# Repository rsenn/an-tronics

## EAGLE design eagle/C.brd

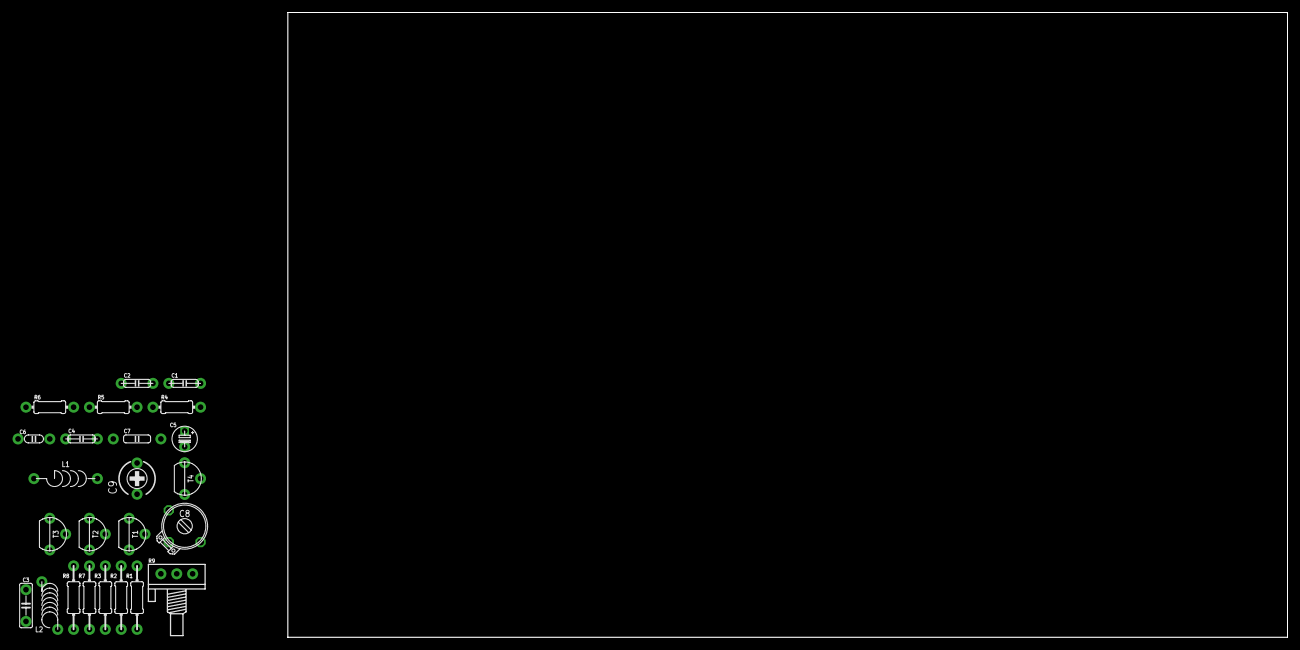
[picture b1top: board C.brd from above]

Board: 2 copper layers, 160.0 x 100.0 mm, 24 parts (0 on the bottom side), 14 nets, no tracks yet.

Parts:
C1, C2: C050-020X044
C3: 10nF; C050-025X060
C4: 10nF; C050-020X044
C5: 100μF; E2.5-4/V
C6: 22pF; C050-020X036
C7: 100nF; C075-020X044
C8: 20pF; TRIM-2222-808
C9: 5pF; CTRIMTZ03
L1: 2.2μH; L-03/10
L2: L-04/8V
R1, R2: 4.7kΩ; 0204/10-V
R3: 0204/10-V
R4, R5: 1MΩ; 0204/7
R6: 56kΩ; 0204/7
R7: 10kΩ; 0204/10-V
R8: 470kΩ; 0204/10-V
R9: 10kΩ; POT
T1, T2, T3, T4: TO92-CBE-A

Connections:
unnamed: C1.2, R5.1, T2.2
unnamed: C2.1, R2.2, R5.2, T2.1
unnamed: C1.1, R1.2, R4.2, T1.1
unnamed: C2.2, R6.1, T3.2
unnamed: C3.1, R3.2, R6.2, T3.1
unnamed: C4.2, R4.1, T1.2
unnamed: C4.1, L1.1
unnamed: C5.+, R1.1, R2.1, R3.1, R7.1, R9.A
unnamed: C7.2, R8.2, T4.2
unnamed: R8.1, R9.S
unnamed: C8.2, C9.2, L2.2, T4.1
unnamed: C6.2, C7.1, L1.2, L2.1, R7.2
unnamed: C6.1, C8.1, C9.1
unnamed: C3.2, C5.-, R9.E, T1.3, T2.3, T3.3, T4.3

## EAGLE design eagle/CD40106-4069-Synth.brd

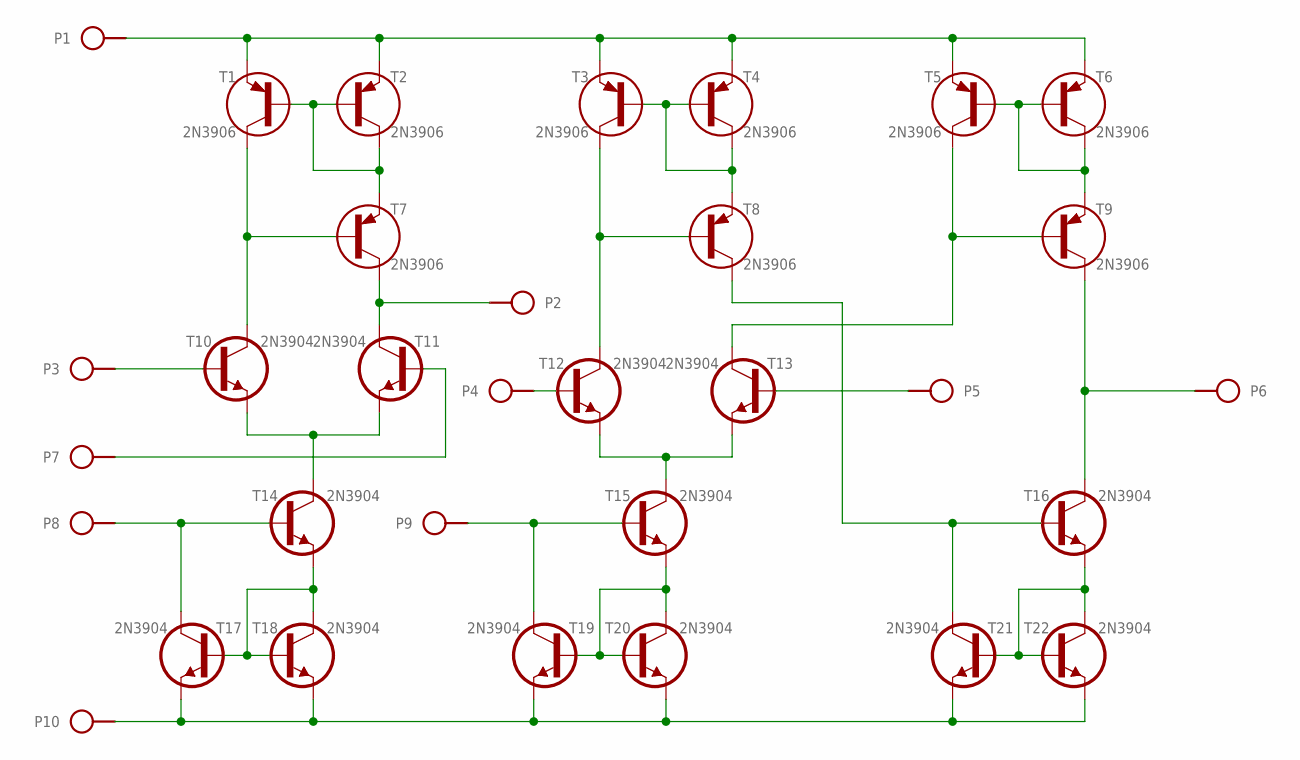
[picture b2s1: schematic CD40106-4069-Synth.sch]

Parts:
P1, P2, P3, P4, P5, P6, P7, P8, P9, P10: SPAD
T1, T2, T3, T4, T5, T6, T7, T8, T9: 2N3906; TO92
T10, T11, T12, T13, T14, T15, T16, T17, T18, T19, T20, T21, T22: 2N3904; TO92

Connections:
+15: P1.1, T1.1 (E), T2.1 (E), T3.1 (E), T4.1 (E), T5.1 (E), T6.1 (E)
-15: P10.1, T17.1 (E), T18.1 (E), T19.1 (E), T20.1 (E), T21.1 (E), T22.1 (E)
IN_A+: P3.1, T10.2 (B)
IN_A-: P7.1, T11.2 (B)
IN_B+: P5.1, T13.2 (B)
IN_B-: P4.1, T12.2 (B)
IO_A: P2.1, T7.3 (C), T11.3 (C)
I_A: P8.1, T14.2 (B), T17.3 (C)
I_B: P9.1, T15.2 (B), T19.3 (C)
unnamed: T1.2 (B), T2.2 (B), T2.3 (C), T7.1 (E)
unnamed: T1.3 (C), T7.2 (B), T10.3 (C)
unnamed: T12.1 (E), T13.1 (E), T15.3 (C)
unnamed: T3.2 (B), T4.2 (B), T4.3 (C), T8.1 (E)
unnamed: T3.3 (C), T8.2 (B), T12.3 (C)
unnamed: T10.1 (E), T11.1 (E), T14.3 (C)
unnamed: T8.3 (C), T16.2 (B), T21.3 (C)
unnamed: T5.2 (B), T6.2 (B), T6.3 (C), T9.1 (E)
unnamed: T5.3 (C), T9.2 (B), T13.3 (C)
unnamed: T14.1 (E), T17.2 (B), T18.2 (B), T18.3 (C)
unnamed: T15.1 (E), T19.2 (B), T20.2 (B), T20.3 (C)
unnamed: T16.1 (E), T21.2 (B), T22.2 (B), T22.3 (C)
OB: P6.1, T9.3 (C), T16.3 (C)

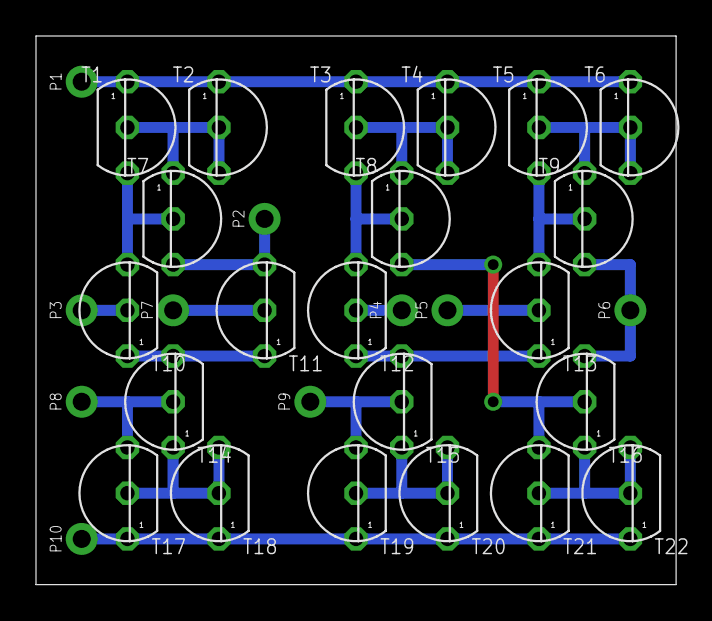
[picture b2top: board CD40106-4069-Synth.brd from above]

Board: 2 copper layers, 35.6 x 30.5 mm, 32 parts (0 on the bottom side), 22 nets.

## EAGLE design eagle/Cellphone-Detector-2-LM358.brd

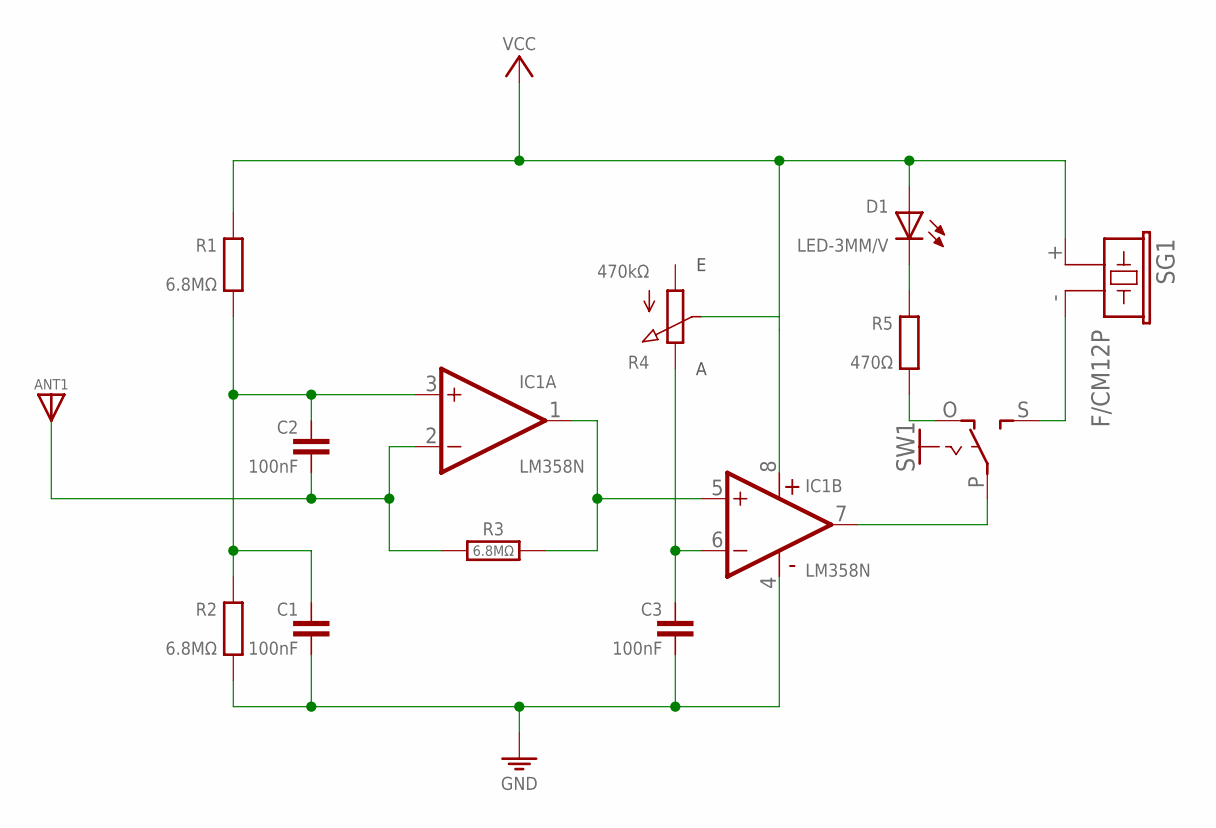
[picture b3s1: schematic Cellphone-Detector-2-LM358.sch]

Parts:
ANT1: ANT; SPAD
C1, C2, C3: 100nF; C025-024X044
D1: LED-3MM/V; LED_3MM/V
IC1: LM358N; DIL08
R1: 6.8MΩ; 0204/7-V
R2: 6.8MΩ; 0204/2V
R3: 6.8MΩ; 0202/2V
R4: 470kΩ; POT-V
R5: 470Ω; 0204/10-V
S1: VCC_GNDPWR-R; PWR-R
SG1: F/CM12P
SW1: SL-SW-1P-2T-V; SLSW-1P2T-V

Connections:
ANT: ANT1.1, C2.2, IC1.2 (-IN), R3.1
GND: C1.2, C3.2, IC1.4 (V-), R2.2 (1), S1.1 (GND)
unnamed: C3.1, IC1.6 (-IN), R4.E
unnamed: SG1.- (2), SW1.S
unnamed: IC1.7 (OUT), SW1.P
unnamed: C1.1, C2.1, IC1.3 (+IN), R1.2 (1), R2.1 (2)
unnamed: D1.K (C), R5.1 (2)
OUT: R5.2 (1), SW1.O
SIG: IC1.1 (OUT), IC1.5 (+IN), R3.2
VCC: D1.A, IC1.8 (V+), R1.1 (2), R4.S, S1.2 (VCC), SG1.+ (1)

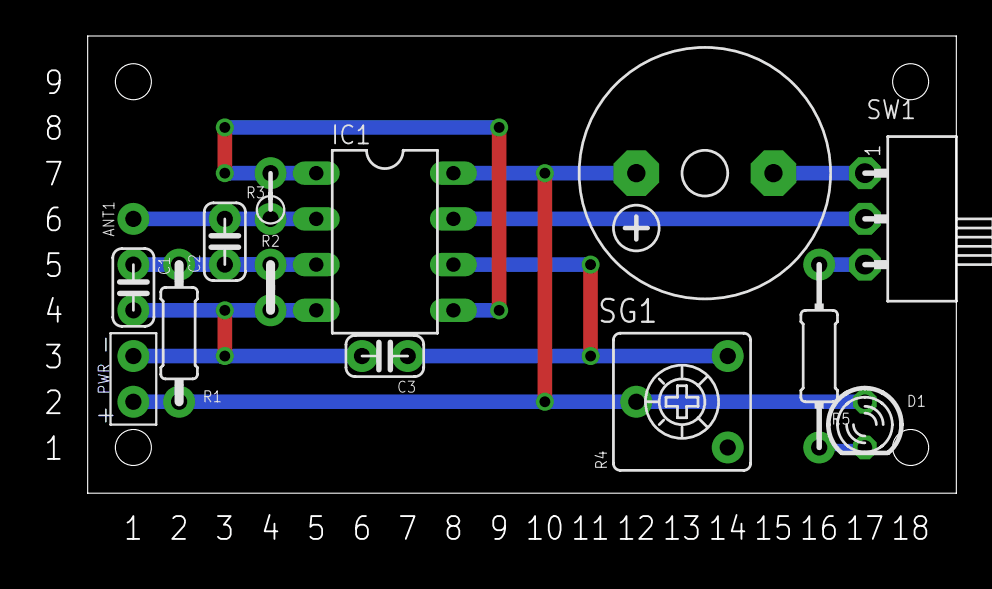
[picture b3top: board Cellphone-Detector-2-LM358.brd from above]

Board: 2 copper layers, 48.3 x 25.4 mm, 14 parts (0 on the bottom side), 10 nets.

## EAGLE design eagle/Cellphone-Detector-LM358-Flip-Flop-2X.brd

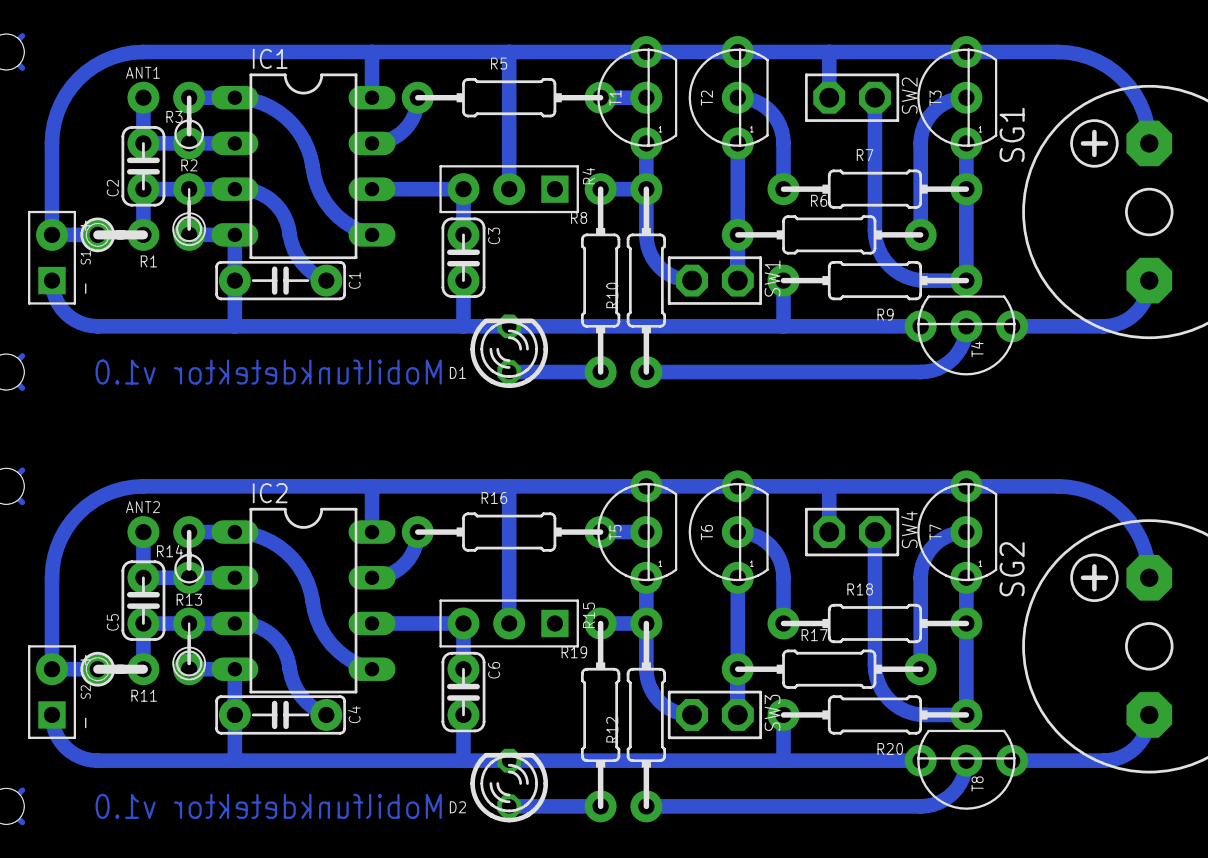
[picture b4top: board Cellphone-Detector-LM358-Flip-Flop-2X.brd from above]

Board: 2 copper layers, 48 parts (0 on the bottom side), 32 nets.

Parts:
ANT1, ANT2: ANT; SPAD
C1, C4: 100nF; C050-025X060
C2, C3, C5, C6: 100nF; C025-024X044
D1, D2: LED rot; LED_3MM/V
IC1, IC2: LM358N; DIL08
R1, R11: 6.8MΩ; 0204/2
R2, R13: 6.8MΩ; 0204/2V
R3, R14: 6.8MΩ; 0202/2V
R4, R15: 470kΩ; CONN-3P
R5, R10, R12, R16: 10kΩ; 0204/10
R6, R7, R17, R18: 22kΩ; 0204/10
R8, R19: 470Ω; 0204/10-V
R9, R20: 1kΩ; 0204/10
S1, S2: VCC_GNDR; SPAD+-
SG1, SG2: F/CM12P
SW1, SW3: SW1; SLSW-1P1T
SW2, SW4: PB-1P-1T-2P; SLSW-1P1T
T1, T2, T3, T5, T6, T7: BC327; TO92
T4, T8: BC337CBE; TO92-CBE

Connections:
ANT: ANT1.1, C2.2, IC1.2, R3.1
ANT1: ANT2.1, C5.2, IC2.2, R14.1
GND: C1.2, C3.2, D1.K, IC1.4, R2.2, R9.2, S1.1, T4.3
GND1: C4.2, C6.2, D2.K, IC2.4, R13.2, R20.2, S2.1, T8.3
unnamed: C3.1, IC1.6, R4.3
unnamed: SG1.-, T4.1
unnamed: IC1.7, R5.1
unnamed: C1.1, C2.1, IC1.3, R1.2, R2.1
unnamed: R7.2, R9.1, SW2.P, T3.1
unnamed: R6.1, SW1.P, T2.1
unnamed: R6.2, T3.2
unnamed: R10.1, T4.2
unnamed: R7.1, T2.2
unnamed: D1.A, R8.2
unnamed: R8.1, R10.2, SW1.S, T1.1
unnamed: R5.2, T1.2
unnamed: C6.1, IC2.6, R15.3
unnamed: C4.1, C5.1, IC2.3, R11.2, R13.1
unnamed: R17.1, SW3.P, T6.1
unnamed: R17.2, T7.2
unnamed: R18.1, T6.2
unnamed: D2.A, R19.2
unnamed: IC2.7, R16.1
unnamed: R16.2, T5.2
unnamed: R12.2, R19.1, SW3.S, T5.1
unnamed: R12.1, T8.2
unnamed: SG2.-, T8.1
unnamed: R18.2, R20.1, SW4.P, T7.1
SIG: IC1.1, IC1.5, R3.2
SIG1: IC2.1, IC2.5, R14.2
VCC: IC1.8, R1.1, R4.2, S1.2, SG1.+, SW2.S, T1.3, T2.3, T3.3
VCC1: IC2.8, R11.1, R15.2, S2.2, SG2.+, SW4.S, T5.3, T6.3, T7.3

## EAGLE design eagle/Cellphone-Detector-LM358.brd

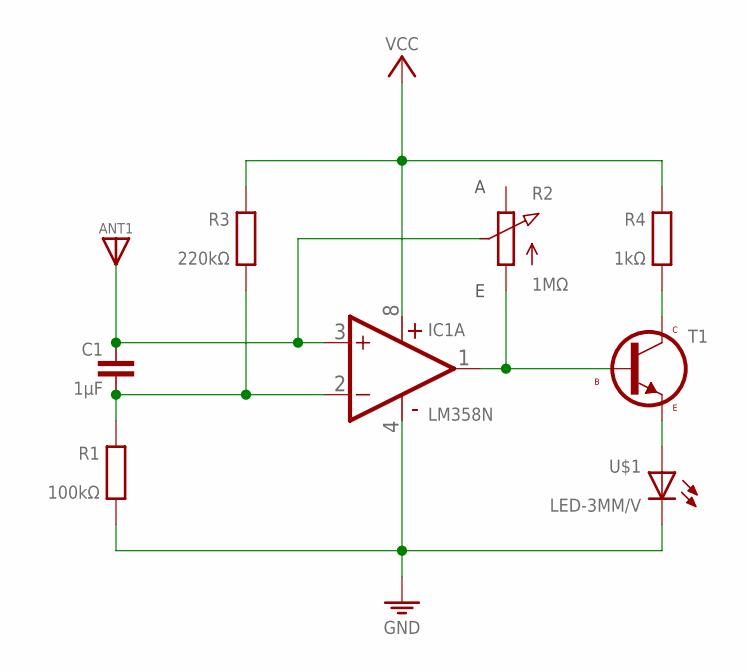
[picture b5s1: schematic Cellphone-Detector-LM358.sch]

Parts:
ANT1: ANT; SPAD
C1: 1µF; C025-024X044
IC1: LM358N; DIL08
R1: 100kΩ; 0202/7-V
R2: 1MΩ; POT-V
R3: 220kΩ; 0204/10-V
R4: 1kΩ; 0204/10-V
S1: VCC_GNDPWR-R; PWR-R
T1: BC547; TO92
U$1: LED-3MM/V; LED_3MM/V

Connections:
GND: IC1.4 (V-), R1.2 (1), S1.1 (GND), U$1.K (C)
unnamed: ANT1.1, C1.1, IC1.3 (+IN), R2.S
unnamed: C1.2, IC1.2 (-IN), R1.1 (2), R3.2 (1)
unnamed: IC1.1 (OUT), R2.A, T1.2 (B)
unnamed: R4.2 (1), T1.1 (C)
unnamed: T1.3 (E), U$1.A
VCC: IC1.8 (V+), R3.1 (2), R4.1 (2), S1.2 (VCC)

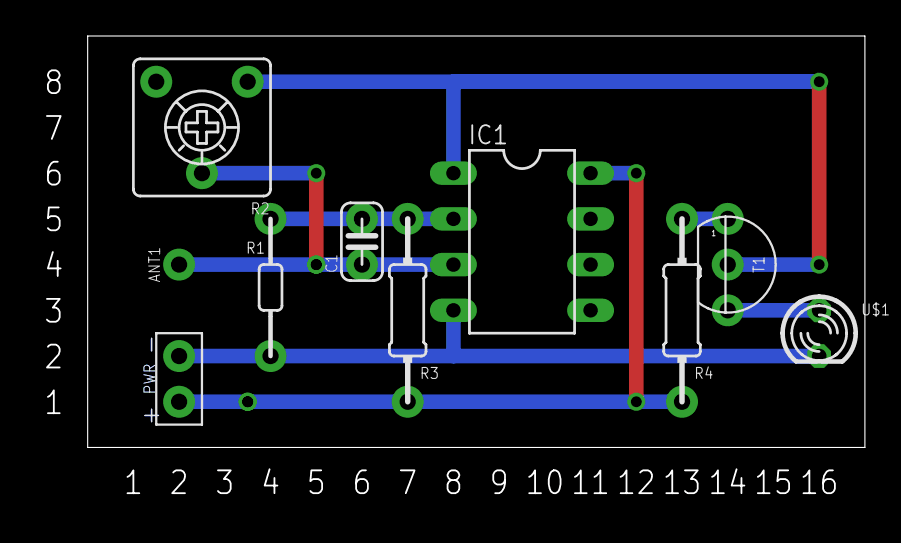
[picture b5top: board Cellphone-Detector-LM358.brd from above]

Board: 2 copper layers, 43.2 x 22.9 mm, 10 parts (0 on the bottom side), 7 nets.

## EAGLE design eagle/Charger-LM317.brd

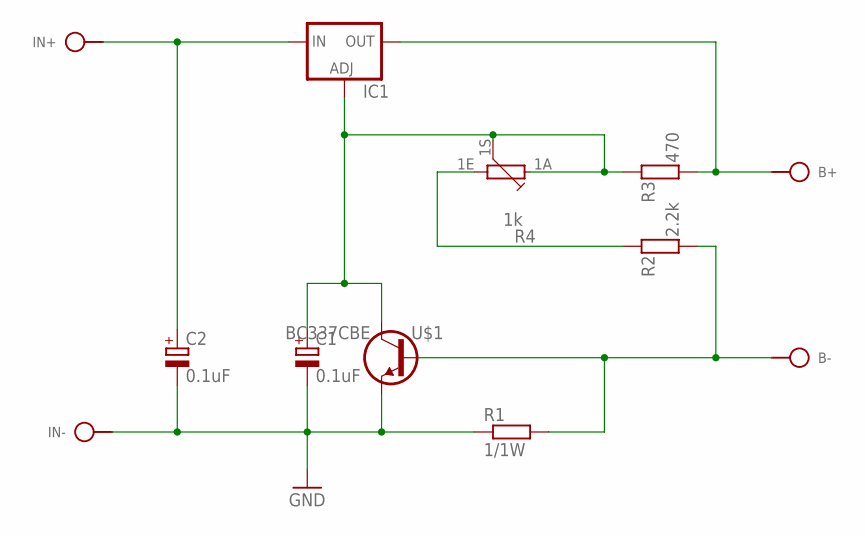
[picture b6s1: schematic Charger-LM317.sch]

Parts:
B+: SPAD
B-: SPAD
C1: 0.1uF; E5-4
C2: 0.1uF; E2,5-4
IC1: LM317TL; 317TL
IN+: SPAD
IN-: SPAD
R1: 1/1W; 0309/12
R2: 2.2k; 0204/10
R3: 470; 0204/10
R4: 1k; PC16S
U$1: BC337CBE; TO92-CBE

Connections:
GND: C1.-, C2.-, IN-.1, R1.1, U$1.E
unnamed: B-.1, R1.2, R2.1, U$1.B
unnamed: R2.2, R4.1E
unnamed: C1.+, IC1.1 (ADJ), R3.2, R4.1A, R4.1S, U$1.C
unnamed: B+.1, IC1.2 (OUT), R3.1
unnamed: C2.+, IC1.3 (IN), IN+.1

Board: 2 copper layers, 12 parts (0 on the bottom side), 6 nets, no tracks yet.

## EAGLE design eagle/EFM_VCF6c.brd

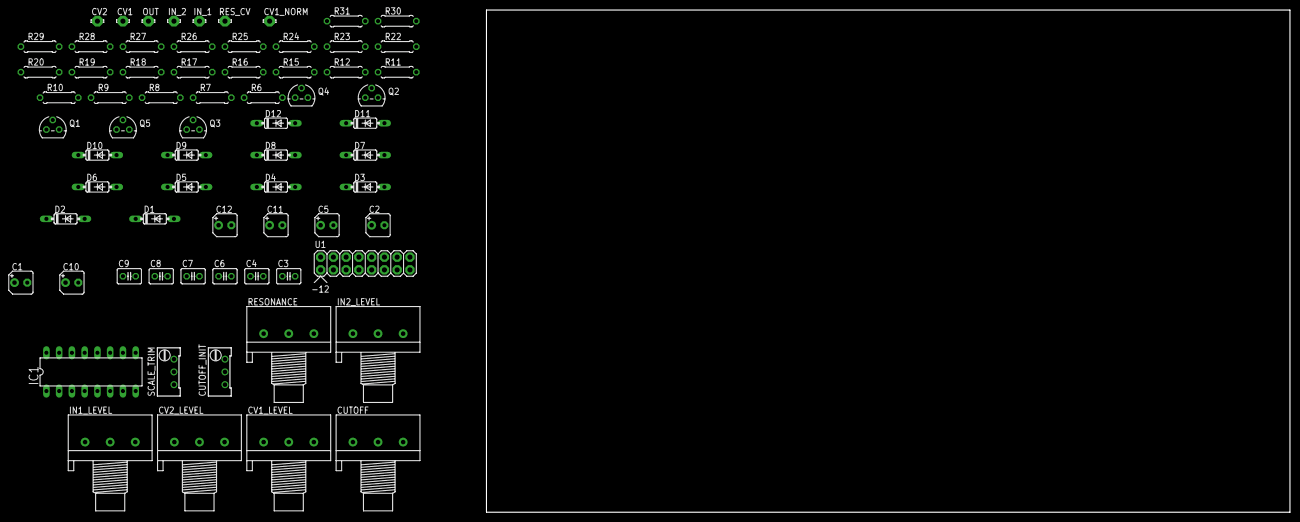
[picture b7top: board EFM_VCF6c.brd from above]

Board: 2 copper layers, 160.0 x 100.0 mm, 69 parts (0 on the bottom side), 47 nets, no tracks yet.

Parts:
C1, C2, C5, C11, C12: 10uF; B45181A
C3, C4, C6, C7, C8, C9: 0.1uF; C025-030X050
C10: 220uF; B45181A
CUTOFF: 100k; 3RP/1610N
CUTOFF_INIT: 100k; RTRIM64W
CV1, CV1_NORM, CV2: LSP10
CV1_LEVEL, CV2_LEVEL: 100k; 3RP/1610N
D1, D2, D3, D4, D5, D6, D7, D8, D9, D10, D11, D12: 1N4148DO35-7; DO35-7
IC1: LM13700N; DIL16
IN1_LEVEL, IN2_LEVEL: 100k; 3RP/1610N
IN_1, IN_2: LSP10
OUT: LSP10
Q1, Q2, Q4: 2N3904; TO92
Q3, Q5: 2N3906; TO92
R6, R7, R8, R9, R10, R11, R26, R30: 100k; 0207/7
R12, R15, R17, R18, R19: 1k; 0207/7
R16: 560k; 0207/7
R20, R23, R28, R29: 10k; 0207/7
R22: 470k; 0207/7
R24, R25: 220k; 0207/7
R27: 1M; 0207/7
R31: 220; 0207/7
RESONANCE: 100k; 3RP/1610N
RES_CV: LSP10
SCALE_TRIM: 2k; RTRIM64W
U1: POWER; POWER_16

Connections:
-12V: C2.-, C4.2, CUTOFF_INIT.1, IC1.6, Q3.1, R23.2, R29.2, U1.1, U1.2
GND: C1.-, C2.+, C3.2, C4.1, C10.-, CUTOFF.1, CV1_LEVEL.1, CV2_LEVEL.1, IC1.13, IN1_LEVEL.1, IN2_LEVEL.1, Q4.3, Q5.2, R19.2, R22.2, R26.2, R31.2, RESONANCE.1, SCALE_TRIM.3, U1.3, U1.4, U1.5, U1.6, U1.7, U1.8
unnamed: IC1.1, R22.1
unnamed: R25.2, RES_CV.MP
unnamed: Q4.1, R17.2
unnamed: Q1.3, Q2.3, R17.1
unnamed: IN2_LEVEL.2, R10.2
unnamed: C5.-, R9.2, R10.1
unnamed: C5.+, Q1.2, R15.1
unnamed: Q3.3, Q4.2, R16.2
unnamed: C6.2, D2.C, D3.A, IC1.4
unnamed: CV2_LEVEL.2, R8.2
unnamed: IC1.5, IC1.7, R30.1
unnamed: C6.1, D8.C, D9.A, IC1.3
unnamed: C7.1, D9.C, D10.A
unnamed: C8.2, D4.C, D5.A
unnamed: C8.1, D10.C, D11.A
unnamed: Q3.2, R6.1, R7.1, R8.1, R11.1, R12.1
unnamed: C9.1, D11.C, D12.A
unnamed: C9.2, D5.C, D6.A
unnamed: D6.C, Q1.1
unnamed: D12.C, Q2.1
unnamed: D1.C, D2.A
unnamed: D7.C, D8.A
unnamed: R24.2, RESONANCE.2
unnamed: Q5.3, R24.1, R25.1, R27.2
unnamed: C10.+, R15.2, R18.2, R19.1, R20.2
unnamed: C11.+, Q2.2, R18.1
unnamed: CUTOFF_INIT.2, R11.2
unnamed: C12.+, IC1.8, R29.1
unnamed: C7.2, D3.C, D4.A
unnamed: IC1.14, R30.2, R31.1
unnamed: C12.-, OUT.MP
unnamed: IC1.16, R28.1
unnamed: Q5.1, R28.2
unnamed: IN2_LEVEL.3, IN_2.MP
unnamed: C11.-, IC1.9, R23.1
unnamed: IC1.10, IC1.12, R26.1
unnamed: R12.2, SCALE_TRIM.2
unnamed: C1.+, C3.1, CUTOFF.3, CUTOFF_INIT.3, D1.A, D7.A, IC1.11, R16.1, R20.1, R27.1, RESONANCE.3, U1.9, U1.10
unnamed: CV1_LEVEL.2, R7.2
unnamed: CV2.MP, CV2_LEVEL.3
unnamed: CV1_NORM.MP, U1.13, U1.14
unnamed: CUTOFF.2, R6.2
unnamed: IN1_LEVEL.2, R9.1
unnamed: IN1_LEVEL.3, IN_1.MP
unnamed: CV1.MP, CV1_LEVEL.3
